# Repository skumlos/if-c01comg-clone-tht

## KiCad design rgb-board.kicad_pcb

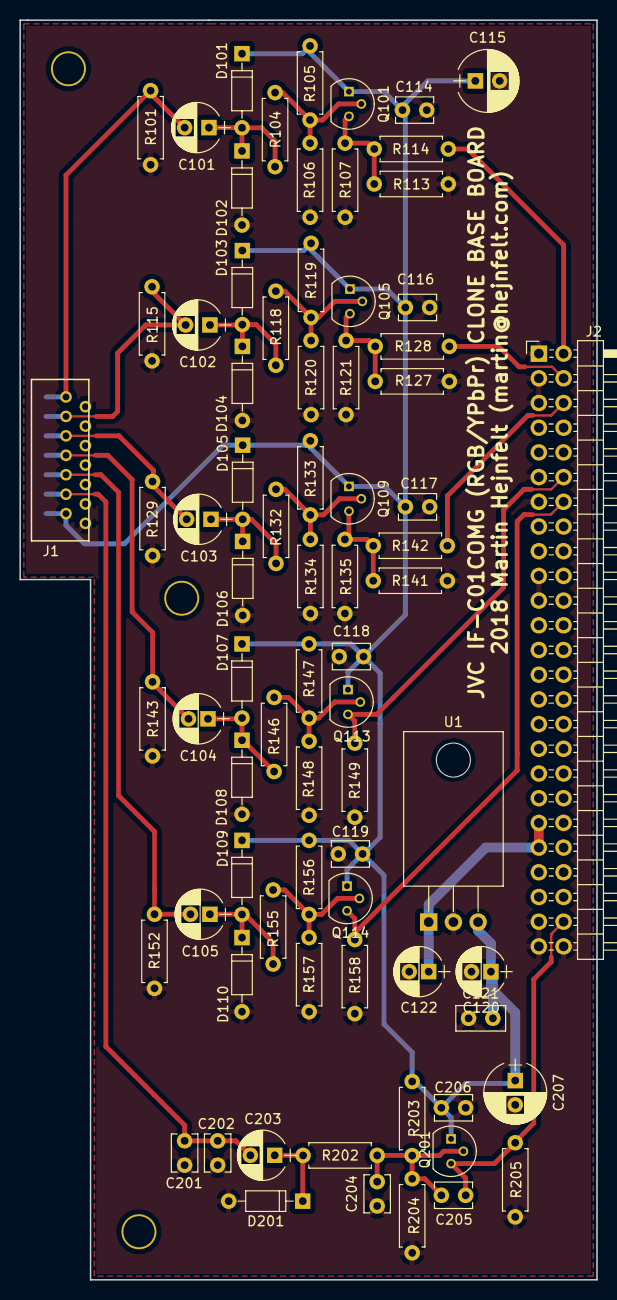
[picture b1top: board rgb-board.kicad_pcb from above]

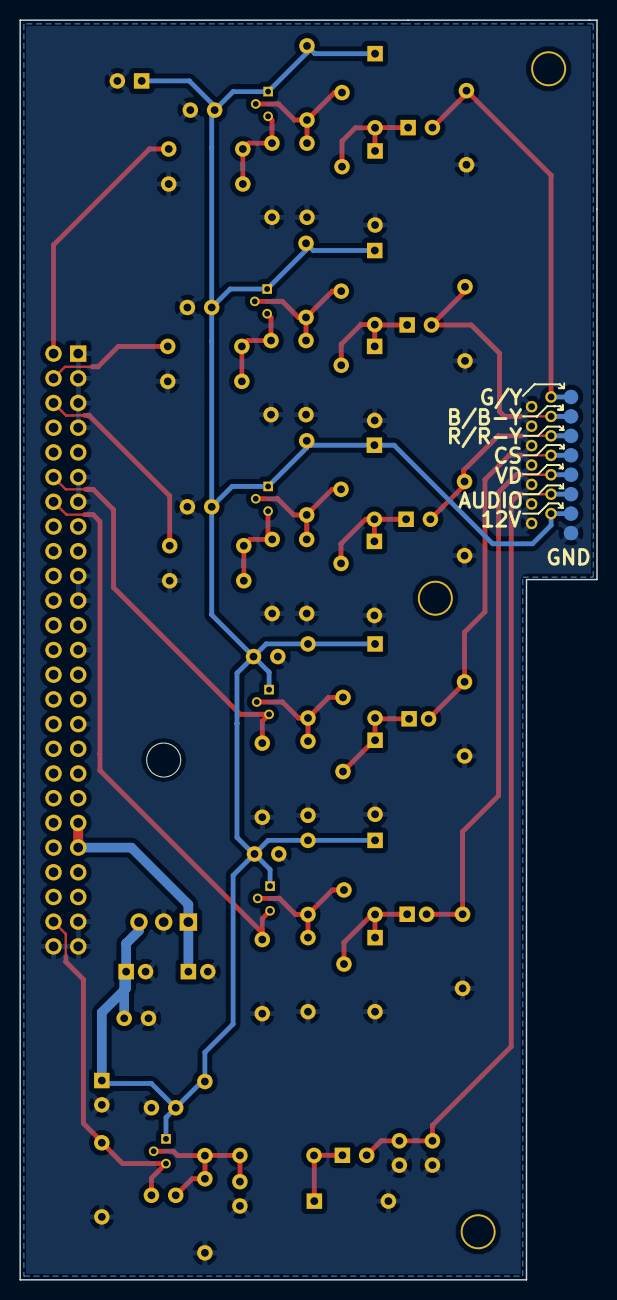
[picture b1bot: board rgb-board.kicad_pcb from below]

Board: 2 copper layers, 59.3 x 129.5 mm, 87 parts (8 on the bottom side), 30 nets.

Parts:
C101, C102, C103: 47uF/25V; CP_Radial_D5.0mm_P2.50mm
C104, C105: 10uF/50V; CP_Radial_D5.0mm_P2.00mm
C114, C116, C117, C118, C119, C206: 100nF; C_Disc_D3.8mm_W2.6mm_P2.50mm
C115, C207: 100uF/16V; CP_Radial_D6.3mm_P2.50mm
C120, C122: 10uF/25V; CP_Radial_D5.0mm_P2.00mm
C121: 1uF/25V; C_Disc_D5.0mm_W2.5mm_P2.50mm
C201, C202, C205: 180pF; C_Disc_D3.8mm_W2.6mm_P2.50mm
C203: 1uF/50V; CP_Radial_D5.0mm_P2.50mm
C204: 39pF; C_Disc_D3.8mm_W2.6mm_P2.50mm
D101, D102, D103, D104, D105, D106, D107, D108, D109, D110: BAT46-TR; D_DO-35_SOD27_P7.62mm_Horizontal
D201: D_Zener; D_DO-35_SOD27_P7.62mm_Horizontal
J1: Conn_01x14; FPC-THT-14P
J2: CONN_02X25; Pin_Header_Angled_2x25_Pitch2.54mm
J3, J4, J5: TEST_1P; MountingHole_3.2mm_M3
J6: TEST_Y; Measurement_Point_Round-SMD-Pad_Small
J7: TEST_B; Measurement_Point_Round-SMD-Pad_Small
J8: TEST_R; Measurement_Point_Round-SMD-Pad_Small
J9: TEST_AUDIO; Measurement_Point_Round-SMD-Pad_Small
J10: TEST_CS; Measurement_Point_Round-SMD-Pad_Small
J11: TEST_VD; Measurement_Point_Round-SMD-Pad_Small
J12: TEST_GND; Measurement_Point_Round-SMD-Pad_Small
J13: TEST_12V; Measurement_Point_Round-SMD-Pad_Small
Q101, Q105, Q109, Q113, Q114, Q201: BC550; TO-92_Molded_Narrow
R101, R115, R129, R143, R152: 75; R_Axial_DIN0207_L6.3mm_D2.5mm_P7.62mm_Horizontal
R104, R114, R118, R128, R132, R142, R146, R155: 100; R_Axial_DIN0207_L6.3mm_D2.5mm_P7.62mm_Horizontal
R105, R119, R133: 56k; R_Axial_DIN0207_L6.3mm_D2.5mm_P7.62mm_Horizontal
R106, R120, R134, R147, R148, R156, R157: 33k; R_Axial_DIN0207_L6.3mm_D2.5mm_P7.62mm_Horizontal
R107, R121, R135: 1.5k; R_Axial_DIN0207_L6.3mm_D2.5mm_P7.62mm_Horizontal
R113, R127, R141: 390; R_Axial_DIN0207_L6.3mm_D2.5mm_P7.62mm_Horizontal
R149, R158: 2.7k; R_Axial_DIN0207_L6.3mm_D2.5mm_P7.62mm_Horizontal
R202: 1K; R_Axial_DIN0207_L6.3mm_D2.5mm_P7.62mm_Horizontal
R203: 56K; R_Axial_DIN0207_L6.3mm_D2.5mm_P7.62mm_Horizontal
R204: 68K; R_Axial_DIN0207_L6.3mm_D2.5mm_P7.62mm_Horizontal
R205: 2.7K; R_Axial_DIN0207_L6.3mm_D2.5mm_P7.62mm_Horizontal
U1: LM7805_TO220; TO-220_Horizontal

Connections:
+12V: C114.2, C115.1, C116.2, C117.2, C118.2, C119.2, C120.1, C121.2, C206.2, C207.1, D101.1, D103.1, D105.1, D107.1, D109.1, J1.13, J13.1, Q101.1, Q105.1, Q109.1, Q113.1, Q114.1, Q201.1, R105.1, R119.1, R133.1, R147.1, R156.1, R203.1, U1.3
/AUDIO: C201.2, C202.2, C203.2, J1.11, J9.1
/AUDIO_: C205.1, J2.48, Q201.3, R205.1
/B-Y: J2.4, R128.2
/B/B-Y: C102.2, J1.3, J7.1, R115.1
/G/Y: C101.2, J1.1, J6.1, R101.1
/HD: J2.12, Q113.3, R149.1
/HD/CS: C104.2, J1.7, J10.1, R143.1
/R-Y: J2.6, R142.2
/R/R-Y: C103.2, J1.5, J8.1, R129.1
/VCC+14V: C122.1, J2.39, J2.41, U1.1
/VD: C105.2, J1.9, J11.1, R152.1
/VD_: J2.14, Q114.3, R158.1
/Y: J2.2, R114.2
GND: C114.1, C115.2, C116.1, C117.1, C118.1, C119.1, C120.2, C121.1, C122.2, C201.1, C202.1, C204.1, C206.1, C207.2, D102.2, D104.2, D106.2, D108.2, D110.2, D201.2, J1.2, J1.4, J1.6, J1.8, J1.10, J1.12, J1.14, J2.1, J2.3, J2.5, J2.7, J2.11, J2.13, J2.19, J2.21, J2.25, J2.31, J2.47, J2.49, J2.50, J12.1, R101.2, R106.2, R107.2, R113.2, R115.2, R120.2, R121.2, R127.2, R129.2, R134.2, R135.2, R141.2, R143.2, R148.2, R149.2, R152.2, R157.2, R158.2, R204.2, R205.2, U1.2
unnamed: C101.1, D101.2, D102.1, R104.2
unnamed: C102.1, D103.2, D104.1, R118.2
unnamed: C103.1, D105.2, D106.1, R132.2
unnamed: C104.1, D107.2, D108.1, R146.2
unnamed: C105.1, D109.2, D110.1, R155.2
unnamed: C203.1, D201.1, R202.2
unnamed: C204.2, C205.2, Q201.2, R202.1, R203.2, R204.1
unnamed: Q101.2, R104.1, R105.2, R106.1
unnamed: Q101.3, R107.1, R113.1, R114.1
unnamed: Q105.2, R118.1, R119.2, R120.1
unnamed: Q105.3, R121.1, R127.1, R128.1
unnamed: Q109.2, R132.1, R133.2, R134.1
unnamed: Q109.3, R135.1, R141.1, R142.1
unnamed: Q113.2, R146.1, R147.2, R148.1
unnamed: Q114.2, R155.1, R156.2, R157.1
